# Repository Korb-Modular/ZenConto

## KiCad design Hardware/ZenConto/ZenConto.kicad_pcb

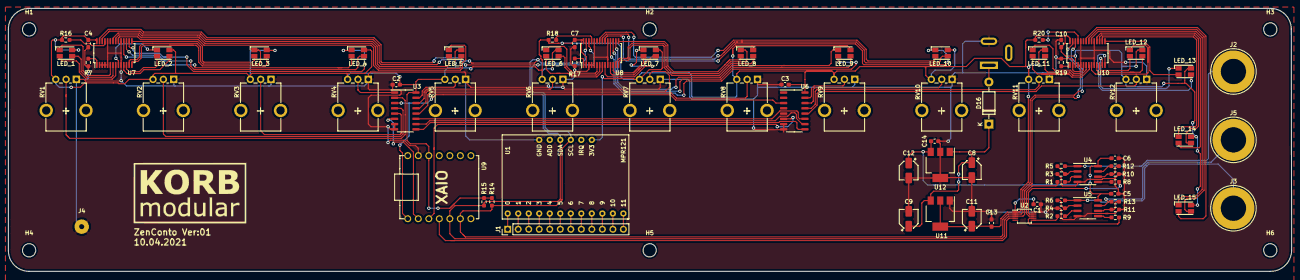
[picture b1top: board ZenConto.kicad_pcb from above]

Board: 2 copper layers, 309.9 x 63.5 mm, 87 parts (1 on the bottom side), 105 nets.

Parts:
C1, C2, C3, C4, C7, C10: 100n; C_0603_1608Metric_Pad1.05x0.95mm_HandSolder
C5, C6, C13, C14: 100nf; C_0603_1608Metric_Pad1.05x0.95mm_HandSolder
C8, C9, C11, C12: 22u; CP_Elec_4x5.4
D16: 1N4001; D_DO-41_SOD81_P10.16mm_Horizontal
H1, H2, H3, H4, H5, H6: MountingHole; MountingHole_3.2mm_M3
J1: Conn_01x12_Female; PinHeader_1x12_P2.54mm_Vertical
J2, J3, J5: Banana_Jack_4mm; Banana_Jack_1Pin
J4: Conn_01x01_Female; SolderWirePad_1x01_Drill1.2mm
J6: Barrel_Jack_Switch; BarrelJack_Wuerth_6941xx301002
LED_1, LED_2, LED_3, LED_4, LED_5, LED_6, LED_7, LED_8, LED_9, LED_10, LED_11, LED_12, LED_13, LED_14, LED_15: RGBA_LED; RGBA_LED_3.2x2.8mm
R1, R2, R8, R9: 1; R_0603_1608Metric_Pad0.98x0.95mm_HandSolder
R3, R4, R5, R6, R10, R11, R12, R13, R16, R18, R20: 10k; R_0603_1608Metric_Pad0.98x0.95mm_HandSolder
R7, R17, R19: 920; R_0603_1608Metric_Pad0.98x0.95mm_HandSolder
R14, R15: 4,7k; R_0603_1608Metric_Pad0.98x0.95mm_HandSolder
RV1, RV2, RV3, RV4, RV5, RV6, RV7, RV8, RV9, RV10, RV11, RV12: R_POT; Potentiometer_Alpha_RD901F-40-00D_Single_Vertical_CircularH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
Ref**: Val**; Logo
U1: MPR121
U2: MCP4728; MSOP-10_3x3mm_P0.5mm
U3, U6: 4051; SO-16_3.9x9.9mm_P1.27mm
U4, U5: LM358; SOIC-8_3.9x4.9mm_P1.27mm
U7, U8, U10: TLC59116; TSSOP-28_4.4x9.7mm_P0.65mm
U9: Xiao
U11: LM1117-3.3; SOT-223-3_TabPin2
U12: LM2937xMP; SOT-223-3_TabPin2

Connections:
+3V3: C1.2, C2.2, C3.2, C4.2, C7.2, C10.2, C11.1, C13.2, LED_1.1, LED_2.1, LED_3.1, LED_4.1, LED_5.1, LED_6.1, LED_7.1, LED_8.1, LED_9.1, LED_10.1, LED_11.1, LED_12.1, LED_13.1, LED_14.1, LED_15.1, R14.1, R15.1, R16.2, R18.2, R20.2, RV1.3, RV2.3, RV3.3, RV4.3, RV5.3, RV6.3, RV7.3, RV8.3, RV9.3, RV10.3, RV11.3, RV12.3, U1.13, U2.1, U3.16, U6.16, U7.28, U8.2, U8.28, U9.12, U10.3, U10.28, U11.2
+10V: C5.2, C6.2, C12.1, C14.2, U4.8, U5.8, U12.3
/Bank1: U3.6, U9.2
/Bank2: U6.6, U9.3
/LDAC: U2.4, U9.4
/LED_1B: LED_1.2, U7.7
/LED_1G: LED_1.4, U7.8
/LED_1R: LED_1.3, U7.6
/LED_2B: LED_2.2, U7.11
/LED_2G: LED_2.4, U7.12
/LED_2R: LED_2.3, U7.9
/LED_3B: LED_3.2, U7.14
/LED_3G: LED_3.4, U7.15
/LED_3R: LED_3.3, U7.13
/LED_4B: LED_4.2, U7.17
/LED_4G: LED_4.4, U7.18
/LED_4R: LED_4.3, U7.16
/LED_5B: LED_5.2, U7.21
/LED_5G: LED_5.4, U7.22
/LED_5R: LED_5.3, U7.20
/LED_6B: LED_6.2, U8.7
/LED_6G: LED_6.4, U8.8
/LED_6R: LED_6.3, U8.6
/LED_7B: LED_7.2, U8.11
/LED_7G: LED_7.4, U8.12
/LED_7R: LED_7.3, U8.9
/LED_8B: LED_8.2, U8.14
/LED_8G: LED_8.4, U8.15
/LED_8R: LED_8.3, U8.13
/LED_9B: LED_9.2, U8.17
/LED_9G: LED_9.4, U8.18
/LED_9R: LED_9.3, U8.16
/LED_10B: LED_10.2, U8.21
/LED_10G: LED_10.4, U8.22
/LED_10R: LED_10.3, U8.20
/LED_11B: LED_11.2, U10.7
/LED_11G: LED_11.4, U10.8
/LED_11R: LED_11.3, U10.6
/LED_12B: LED_12.2, U10.11
/LED_12G: LED_12.4, U10.12
/LED_12R: LED_12.3, U10.9
/LED_13B: LED_13.2, U10.14
/LED_13G: LED_13.4, U10.15
/LED_13R: LED_13.3, U10.13
/LED_14B: LED_14.2, U10.17
/LED_14G: LED_14.4, U10.18
/LED_14R: LED_14.3, U10.16
/LED_15B: LED_15.2, U10.21
/LED_15G: LED_15.4, U10.22
/LED_15R: LED_15.3, U10.20
/Mult: U3.3, U6.3, U9.1
/Pot1: RV3.2, U3.5
/Pot2: RV2.2, U3.4
/Pot3: RV1.2, U3.2
/Pot4: RV4.2, U3.1
/Pot5: RV5.2, U3.15
/Pot6: RV6.2, U3.14
/Pot7: RV7.2, U3.13
/Pot8: RV8.2, U3.12
/Pot9: RV9.2, U6.15
/Pot10: RV10.2, U6.14
/Pot11: RV11.2, U6.13
/Pot12: RV12.2, U6.12
/S0: U3.11, U6.11
/S1: U3.10, U6.10
/S2: U3.9, U6.9
/SCL: R14.2, U1.15, U2.2, U7.26, U8.26, U9.6, U10.26
/SDA: R15.2, U1.16, U2.3, U7.27, U8.27, U9.5, U10.27
/VOUTA: R2.2, U2.6
/VOUTB: R9.2, U2.7
/VOUTC: R1.2, U2.8
/VOUTD: R8.2, U2.9
GND: C1.1, C2.1, C3.1, C4.1, C5.1, C6.1, C7.1, C8.2, C9.2, C10.1, C11.2, C12.2, C13.1, C14.1, J4.1, J6.2, R3.2, R4.2, R7.1, R10.2, R11.2, R17.1, R19.1, RV1.1, RV2.1, RV3.1, RV4.1, RV5.1, RV6.1, RV7.1, RV8.1, RV9.1, RV10.1, RV11.1, RV12.1, U1.18, U2.10, U3.7, U3.8, U4.4, U5.4, U6.7, U6.8, U7.2, U7.3, U7.4, U7.5, U7.10, U7.19, U7.24, U8.3, U8.4, U8.5, U8.10, U8.19, U8.24, U9.13, U10.2, U10.4, U10.5, U10.10, U10.19, U10.24, U11.1, U12.2
unnamed: C8.1, C9.1, D16.1, U11.3, U12.1
unnamed: D16.2, J6.1
unnamed: J1.1, U1.1
unnamed: J1.2, U1.2
unnamed: J1.3, U1.3
unnamed: J1.4, U1.4
unnamed: J1.5, U1.5
unnamed: J1.6, U1.6
unnamed: J1.7, U1.7
unnamed: J1.8, U1.8
unnamed: J1.9, U1.9
unnamed: J1.10, U1.10
unnamed: J1.11, U1.11
unnamed: J1.12, U1.12
unnamed: J2.1, R5.1, U4.1
unnamed: J3.1, R6.1, U5.1
unnamed: J5.1, R13.1, U5.7
unnamed: R1.1, U4.3
unnamed: R2.1, U5.3
unnamed: R3.1, R5.2, U4.2
unnamed: R4.1, R6.2, U5.2
unnamed: R7.2, U7.1
unnamed: R8.1, U4.5
unnamed: R9.1, U5.5
unnamed: R10.1, R12.2, U4.6
unnamed: R11.1, R13.2, U5.6
unnamed: R12.1, U4.7
unnamed: R16.1, U7.25
unnamed: R17.2, U8.1
unnamed: R18.1, U8.25
unnamed: R19.2, U10.1
unnamed: R20.1, U10.25

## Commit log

2021-04-10 PCB V01
    Gerber Files created, PCB ordered
